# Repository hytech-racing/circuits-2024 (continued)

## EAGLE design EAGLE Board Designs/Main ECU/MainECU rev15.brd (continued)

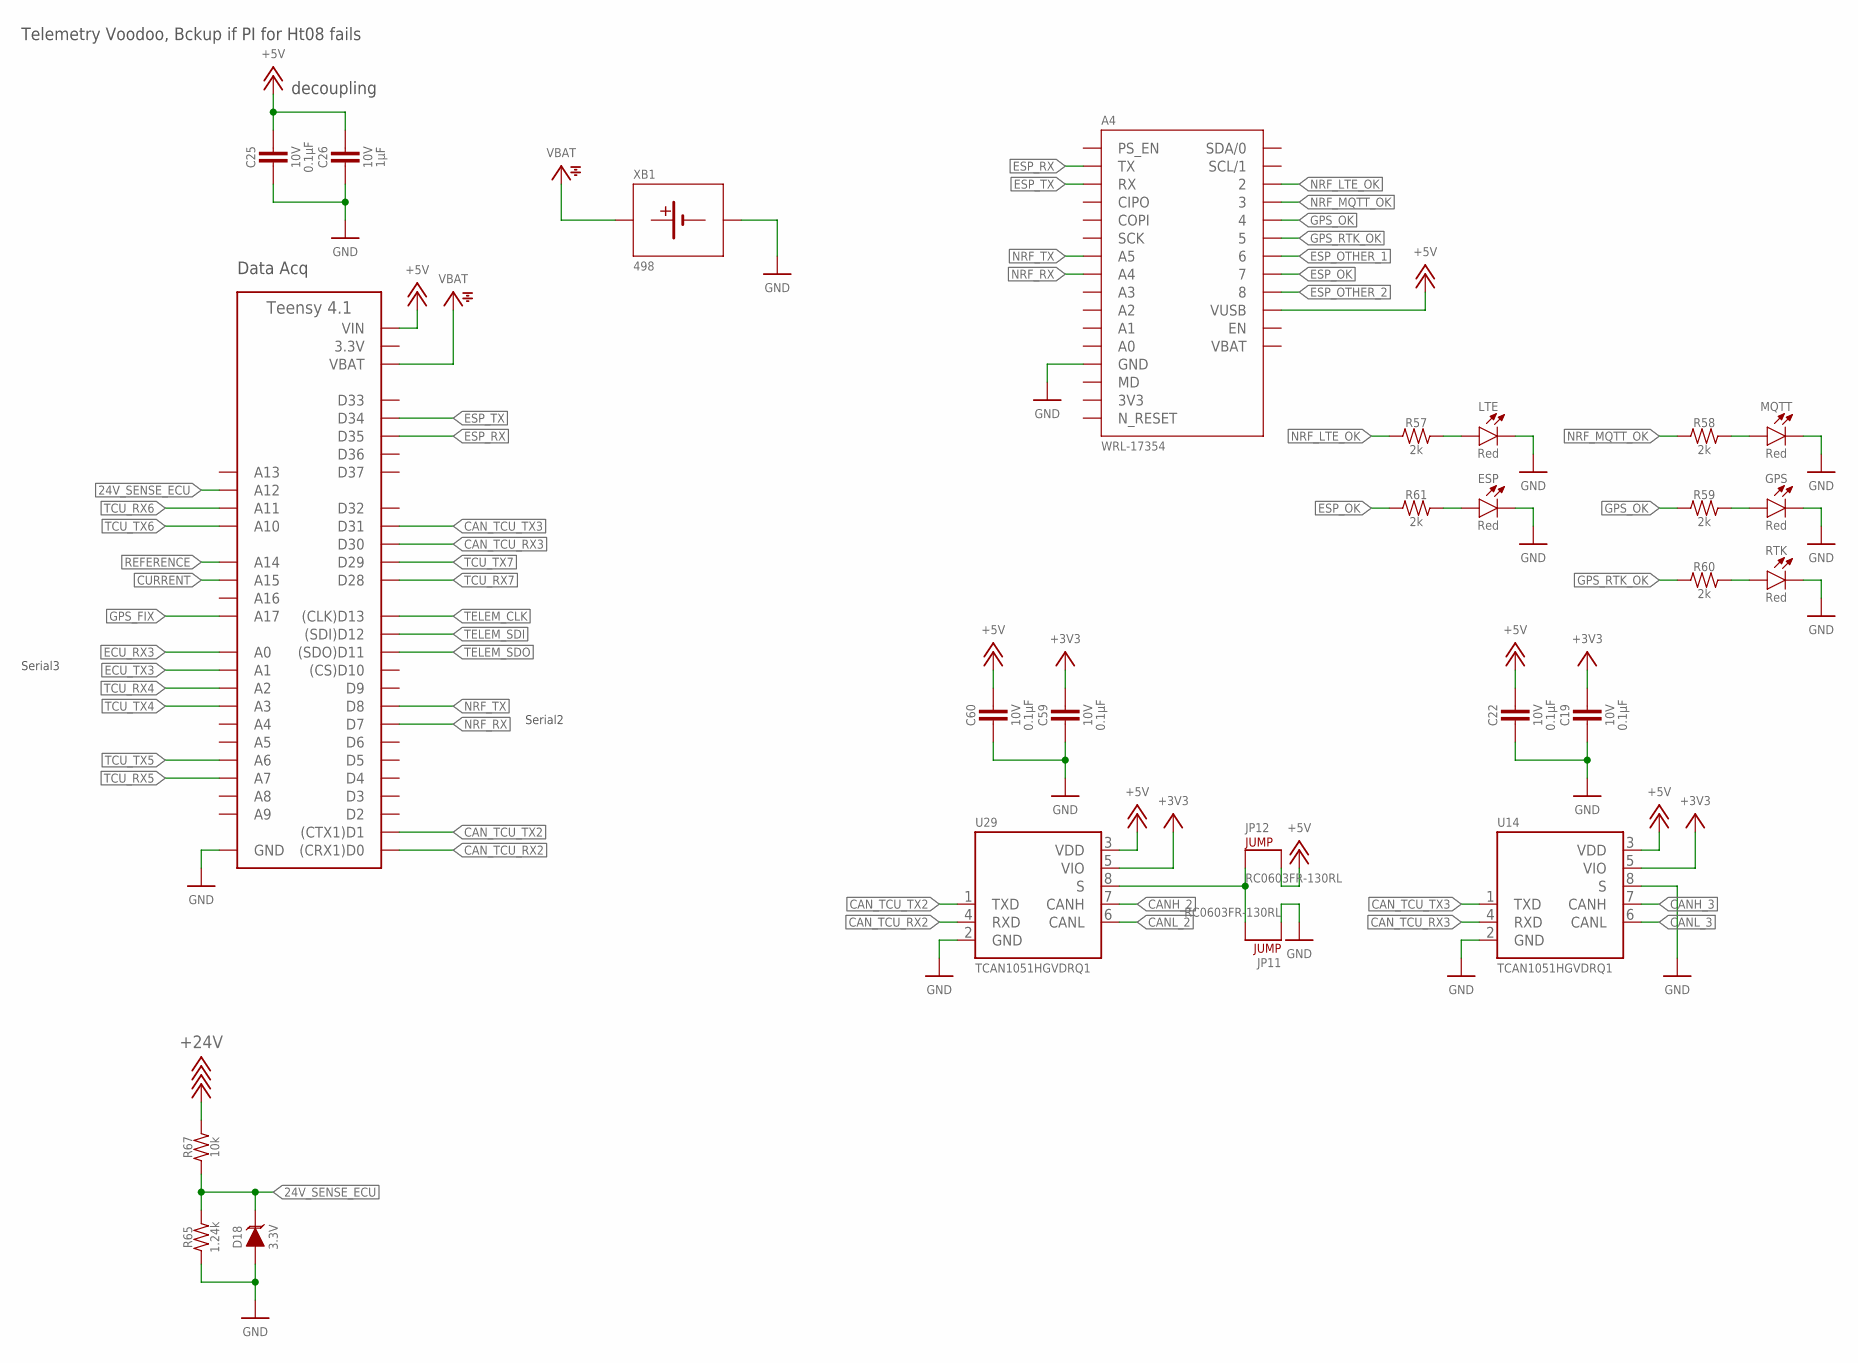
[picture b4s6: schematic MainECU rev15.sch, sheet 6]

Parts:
A3: TEENSY_4.1; TEENSY_LONG_EXT
A4: NRF9160LTE
C19, C22, C25, C59, C60: CAPACITOR_0603_10V_0.1UF; 0603-CAP
C26: CAPACITOR_0603_10V_1UF; 0603-CAP
D18: TVS__5V; SOT-23; VOLTAGE 3.3V; MPN GSOT03-E3-08
ESP: LED_0603_RED; 0603-LED
GPS: LED_0603_RED; 0603-LED
JP11: DNP; 0603-RES
JP12: JUMPER_0603_; 0603-RES
LTE: LED_0603_RED; 0603-LED
MQTT: LED_0603_RED; 0603-LED
R57, R58, R59, R60, R61: RESISTOR_0603_2K; 0603-RES
R65: RESISTOR_0603_1.24K; 0603-RES
R67: RESISTOR_0603_10K; 0603-RES
RTK: LED_0603_RED; 0603-LED
U14, U29: TCAN1051HQV-Q1; SOIC-08(NARROW,0.15")
XB1: BATTERY_HOLDER_KEYSTONE_498; 498

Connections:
3.3V: A3.3V3 (3.3V), A3.3V3@2 (3.3V), A3.3V3@3 (3.3V); also elsewhere on the board
3V3: A4.3V3
24V_SENSE_ECU: A3.D26 (A12), D18.3 (C), R65.2, R67.1; also elsewhere on the board
+3V3: C19.1, C59.1, U14.5 (VIO), U29.5 (VIO); also elsewhere on the board
+5V: A3.VIN, A4.VUSB, C22.1, C25.1, C26.1, C60.1, JP12.2, U14.3 (VDD), U29.3 (VDD); also elsewhere on the board
+24V: R67.2; also elsewhere on the board
CANH_2: U29.7 (CANH); also elsewhere on the board
CANH_3: U14.7 (CANH); also elsewhere on the board
CANL_2: U29.6 (CANL); also elsewhere on the board
CANL_3: U14.6 (CANL); also elsewhere on the board
CAN_TCU_RX2: A3.D0 ((CRX1)D0), U29.4 (RXD)
CAN_TCU_RX3: A3.D30, U14.4 (RXD)
CAN_TCU_TX2: A3.D1 ((CTX1)D1), U29.1 (TXD)
CAN_TCU_TX3: A3.D31, U14.1 (TXD)
CURRENT: A3.D39 (A15); also elsewhere on the board
ECU_RX3: A3.D14 (A0); also elsewhere on the board
ECU_TX3: A3.D15 (A1); also elsewhere on the board
ESP_OK: A4.7, R61.1
ESP_OTHER_1: A4.6
ESP_OTHER_2: A4.8
ESP_RX: A3.D35, A4.TX
ESP_TX: A3.D34, A4.RX
GND: A3.AGND/GND (GND), A3.GND, A3.GND@2 (GND), A4.GND, C19.2, C22.2, C25.2, C26.2, C59.2, C60.2, D18.1 (A), ESP.1 (C), GPS.1 (C), JP11.1, LTE.1 (C), MQTT.1 (C), R65.1, RTK.1 (C), U14.2 (GND), U14.8 (S), U29.2 (GND), XB1.2 (MINUS); also elsewhere on the board
GPS_FIX: A3.D41 (A17)
GPS_OK: A4.4, R59.1
GPS_RTK_OK: A4.5, R60.1
unnamed: ESP.2 (A), R61.2
unnamed: JP11.2, JP12.1, U29.8 (S)
unnamed: LTE.2 (A), R57.2
unnamed: MQTT.2 (A), R58.2
unnamed: GPS.2 (A), R59.2
unnamed: R60.2, RTK.2 (A)
NRF_LTE_OK: A4.2, R57.1
NRF_MQTT_OK: A4.3, R58.1
NRF_RX: A3.D7, A4.A4
NRF_TX: A3.D8, A4.A5
REFERENCE: A3.D38 (A14); also elsewhere on the board
TCU_RX4: A3.D16 (A2)
TCU_RX5: A3.D21 (A7)
TCU_RX6: A3.D25 (A11)
TCU_RX7: A3.D28
TCU_TX4: A3.D17 (A3)
TCU_TX5: A3.D20 (A6)
TCU_TX6: A3.D24 (A10)
TCU_TX7: A3.D29
TELEM_CLK: A3.D13 ((CLK)D13)
TELEM_SDI: A3.D12 ((SDI)D12)
TELEM_SDO: A3.D11 ((SDO)D11)
VBAT: A3.VBAT, A4.VBAT, XB1.1 (PLUS)

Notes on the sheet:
decoupling
Data Acq
Serial2
Serial3
Telemetry Voodoo, Bckup if PI for Ht08 fails

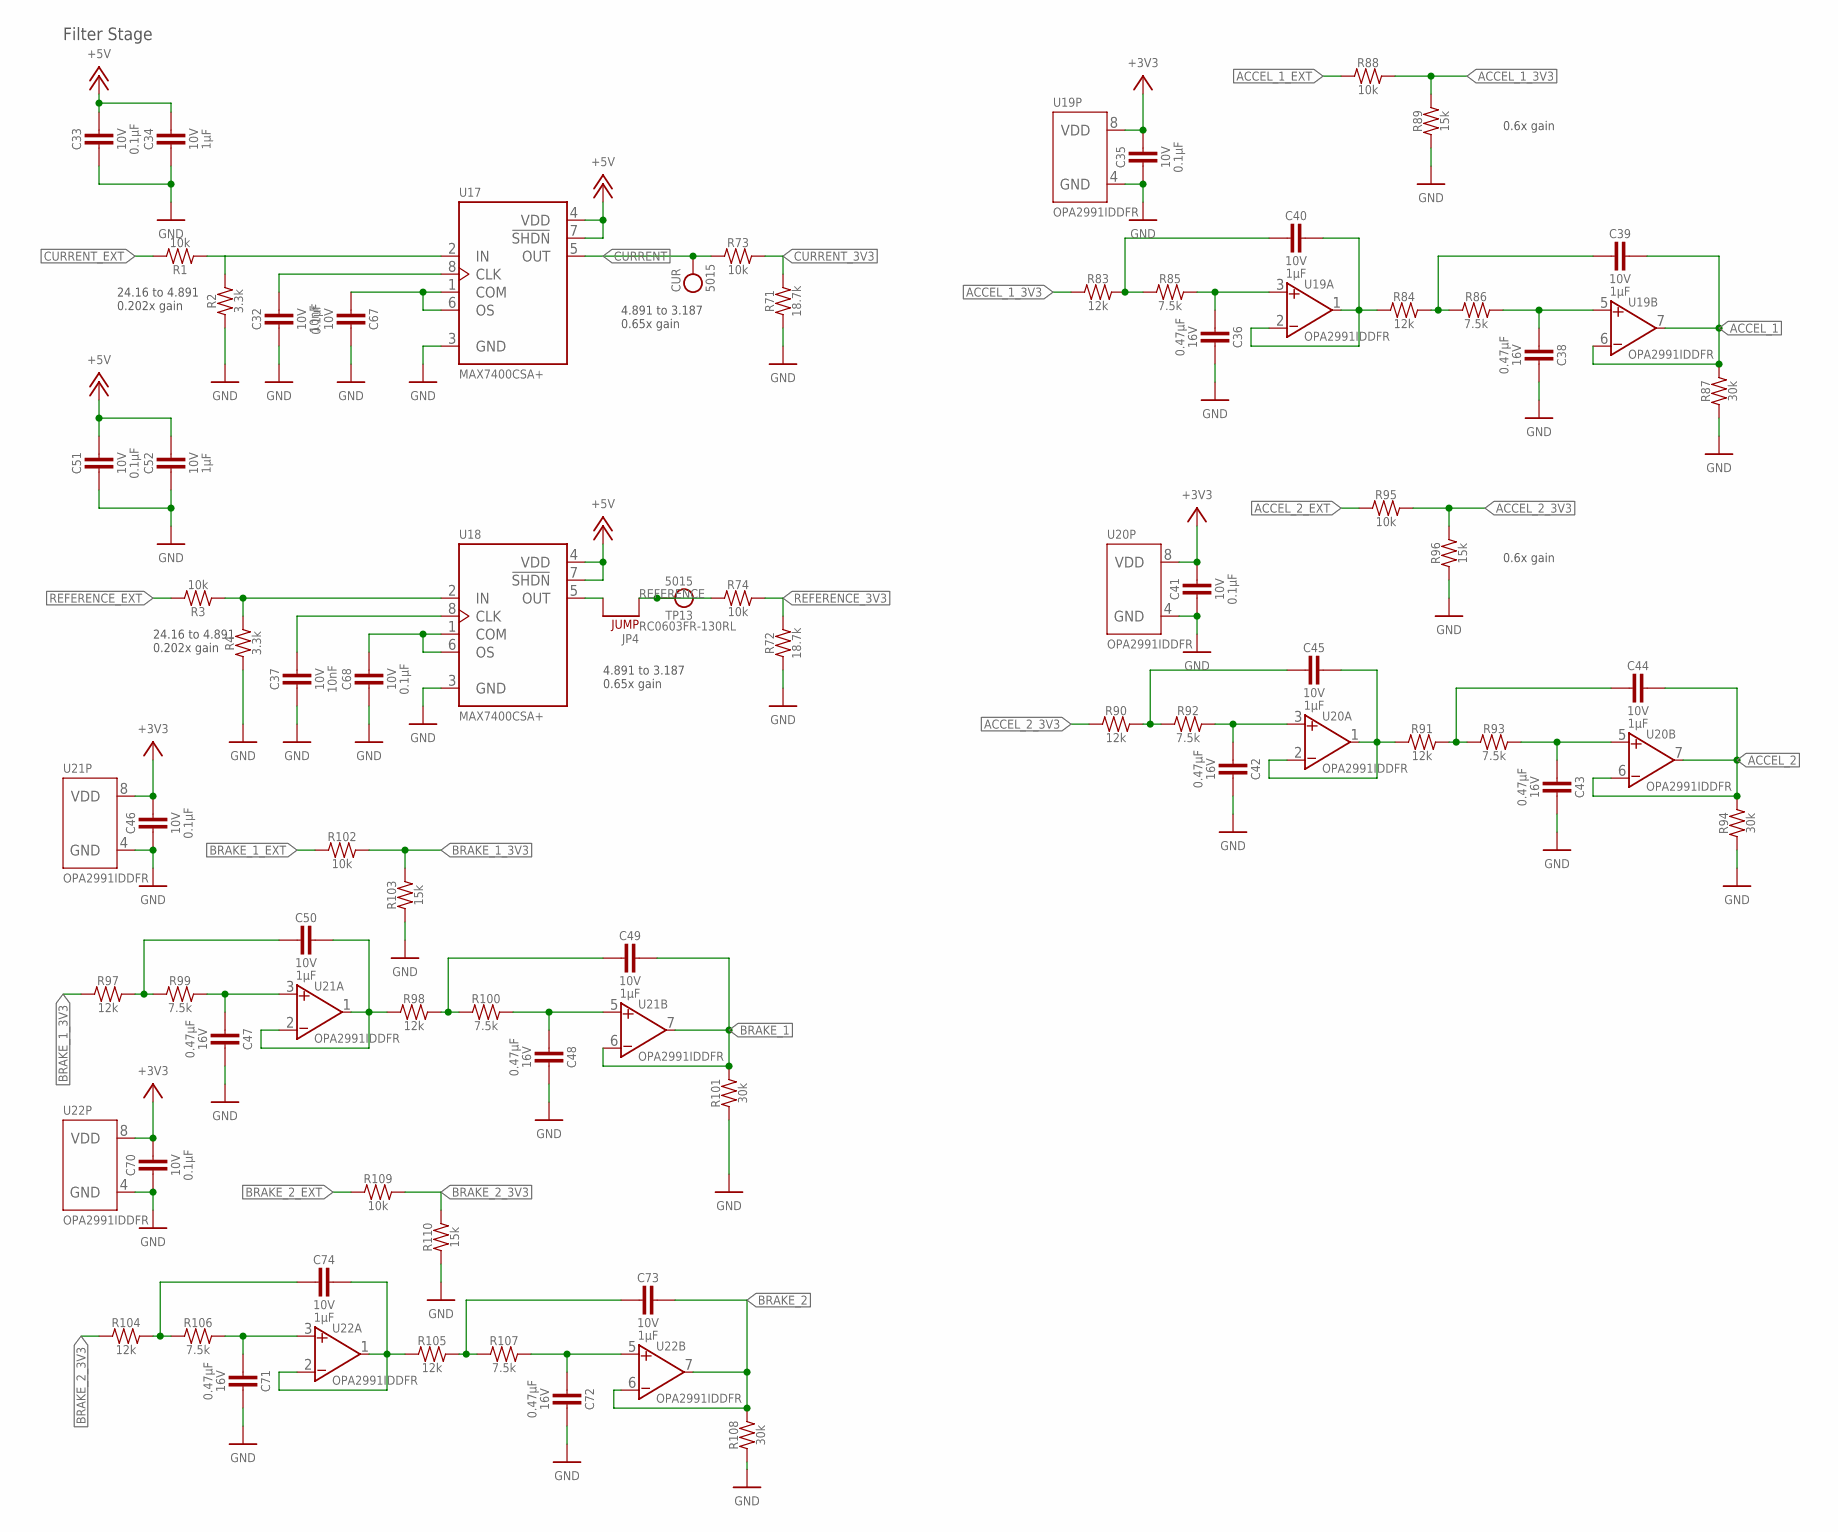
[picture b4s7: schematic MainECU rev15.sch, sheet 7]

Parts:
C32, C37: CAPACITOR_0603_10V_10NF; 0603-CAP
C33, C35, C41, C46, C51, C67, C68, C70: CAPACITOR_0603_10V_0.1UF; 0603-CAP
C34, C39, C40, C44, C45, C49, C50, C52, C73, C74: CAPACITOR_0603_10V_1UF; 0603-CAP
C36, C38, C42, C43, C47, C48, C71, C72: CAPACITOR_0603_16V_0.47UF; 0603-CAP
CUR: TEST_POINT; 5015
JP4: JUMPER_0603_; 0603-RES
R1, R3, R73, R74, R88, R95, R102, R109: RESISTOR_0603_10K; 0603-RES
R2, R4: RESISTOR_0603_3.3K; 0603-RES
R71, R72: RESISTOR_0603_18.7K; 0603-RES
R83, R84, R90, R91, R97, R98, R104, R105: RESISTOR_0603_12K; 0603-RES
R85, R86, R92, R93, R99, R100, R106, R107: RESISTOR_0603_7.5K; 0603-RES
R87, R94, R101, R108: RESISTOR_0603_30K; 0603-RES
R89, R96, R103, R110: RESISTOR_0603_15K; 0603-RES
TP13: TEST_POINT; 5015
U17, U18: MAX7400; SOIC-08(NARROW,0.15")
U19, U20, U21, U22: OPAMP_2_CHANNEL_OPA_2991; SOT-23-8

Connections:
+3V3: C35.1, C41.1, C46.1, C70.1, U19.8 (VDD), U20.8 (VDD), U21.8 (VDD), U22.8 (VDD); also elsewhere on the board
+5V: C33.1, C34.1, C51.1, C52.1, U17.4 (VDD), U17.7 (!SHDN), U18.4 (VDD), U18.7 (!SHDN); also elsewhere on the board
ACCEL_1: C39.1, R87.2, U19.6 (VIN-), U19.7 (VOUT); also elsewhere on the board
ACCEL_1_3V3: R83.1, R88.2, R89.2
ACCEL_1_EXT: R88.1; also elsewhere on the board
ACCEL_2: C44.1, R94.2, U20.6 (VIN-), U20.7 (VOUT); also elsewhere on the board
ACCEL_2_3V3: R90.1, R95.2, R96.2
ACCEL_2_EXT: R95.1; also elsewhere on the board
BRAKE_1: C49.1, R101.2, U21.6 (VIN-), U21.7 (VOUT); also elsewhere on the board
BRAKE_1_3V3: R97.1, R102.2, R103.2
BRAKE_1_EXT: R102.1; also elsewhere on the board
BRAKE_2: C73.1, R108.2, U22.6 (VIN-), U22.7 (VOUT); also elsewhere on the board
BRAKE_2_3V3: R104.1, R109.2, R110.2
BRAKE_2_EXT: R109.1; also elsewhere on the board
CURRENT: CUR.1, R73.1, U17.5 (OUT); also elsewhere on the board
CURRENT_3V3: R71.2, R73.2; also elsewhere on the board
CURRENT_EXT: R1.2; also elsewhere on the board
CURRENT_PRE: R1.1, R2.2, U17.2 (IN)
GND: C32.2, C33.2, C34.2, C35.2, C36.1, C37.2, C38.1, C41.2, C42.1, C43.1, C46.2, C47.1, C48.1, C51.2, C52.2, C67.1, C68.2, C70.2, C71.1, C72.1, R2.1, R4.1, R71.1, R72.1, R87.1, R89.1, R94.1, R96.1, R101.1, R103.1, R108.1, R110.1, U17.3 (GND), U18.3 (GND), U19.4 (GND), U20.4 (GND), U21.4 (GND), U22.4 (GND); also elsewhere on the board
unnamed: C40.2, R83.2, R85.1
unnamed: C36.2, R85.2, U19.3 (VIN+)
unnamed: C39.2, R84.2, R86.1
unnamed: C40.1, R84.1, U19.1 (VOUT), U19.2 (VIN-)
unnamed: C38.2, R86.2, U19.5 (VIN+)
unnamed: C43.2, R93.2, U20.5 (VIN+)
unnamed: JP4.2, U18.5 (OUT)
unnamed: C42.2, R92.2, U20.3 (VIN+)
unnamed: C37.1, U18.8 (CLK)
unnamed: C45.1, R91.1, U20.1 (VOUT), U20.2 (VIN-)
unnamed: C44.2, R91.2, R93.1
unnamed: C45.2, R90.2, R92.1
unnamed: C50.2, R97.2, R99.1
unnamed: C68.1, U18.1 (COM), U18.6 (OS)
unnamed: C32.1, U17.8 (CLK)
unnamed: C47.2, R99.2, U21.3 (VIN+)
unnamed: C67.2, U17.1 (COM), U17.6 (OS)
unnamed: C50.1, R98.1, U21.1 (VOUT), U21.2 (VIN-)
unnamed: C49.2, R98.2, R100.1
unnamed: C48.2, R100.2, U21.5 (VIN+)
unnamed: C74.2, R104.2, R106.1
unnamed: C71.2, R106.2, U22.3 (VIN+)
unnamed: C74.1, R105.1, U22.1 (VOUT), U22.2 (VIN-)
unnamed: C73.2, R105.2, R107.1
unnamed: C72.2, R107.2, U22.5 (VIN+)
REFERENCE: JP4.1, R74.1, TP13.1; also elsewhere on the board
REFERENCE_3V3: R72.2, R74.2; also elsewhere on the board
REFERENCE_EXT: R3.2; also elsewhere on the board
REFERNECE_PRE: R3.1, R4.2, U18.2 (IN)

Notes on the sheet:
24.16 to 4.891 0.202x gain
Filter Stage
4.891 to 3.187 0.65x gain
0.6x gain

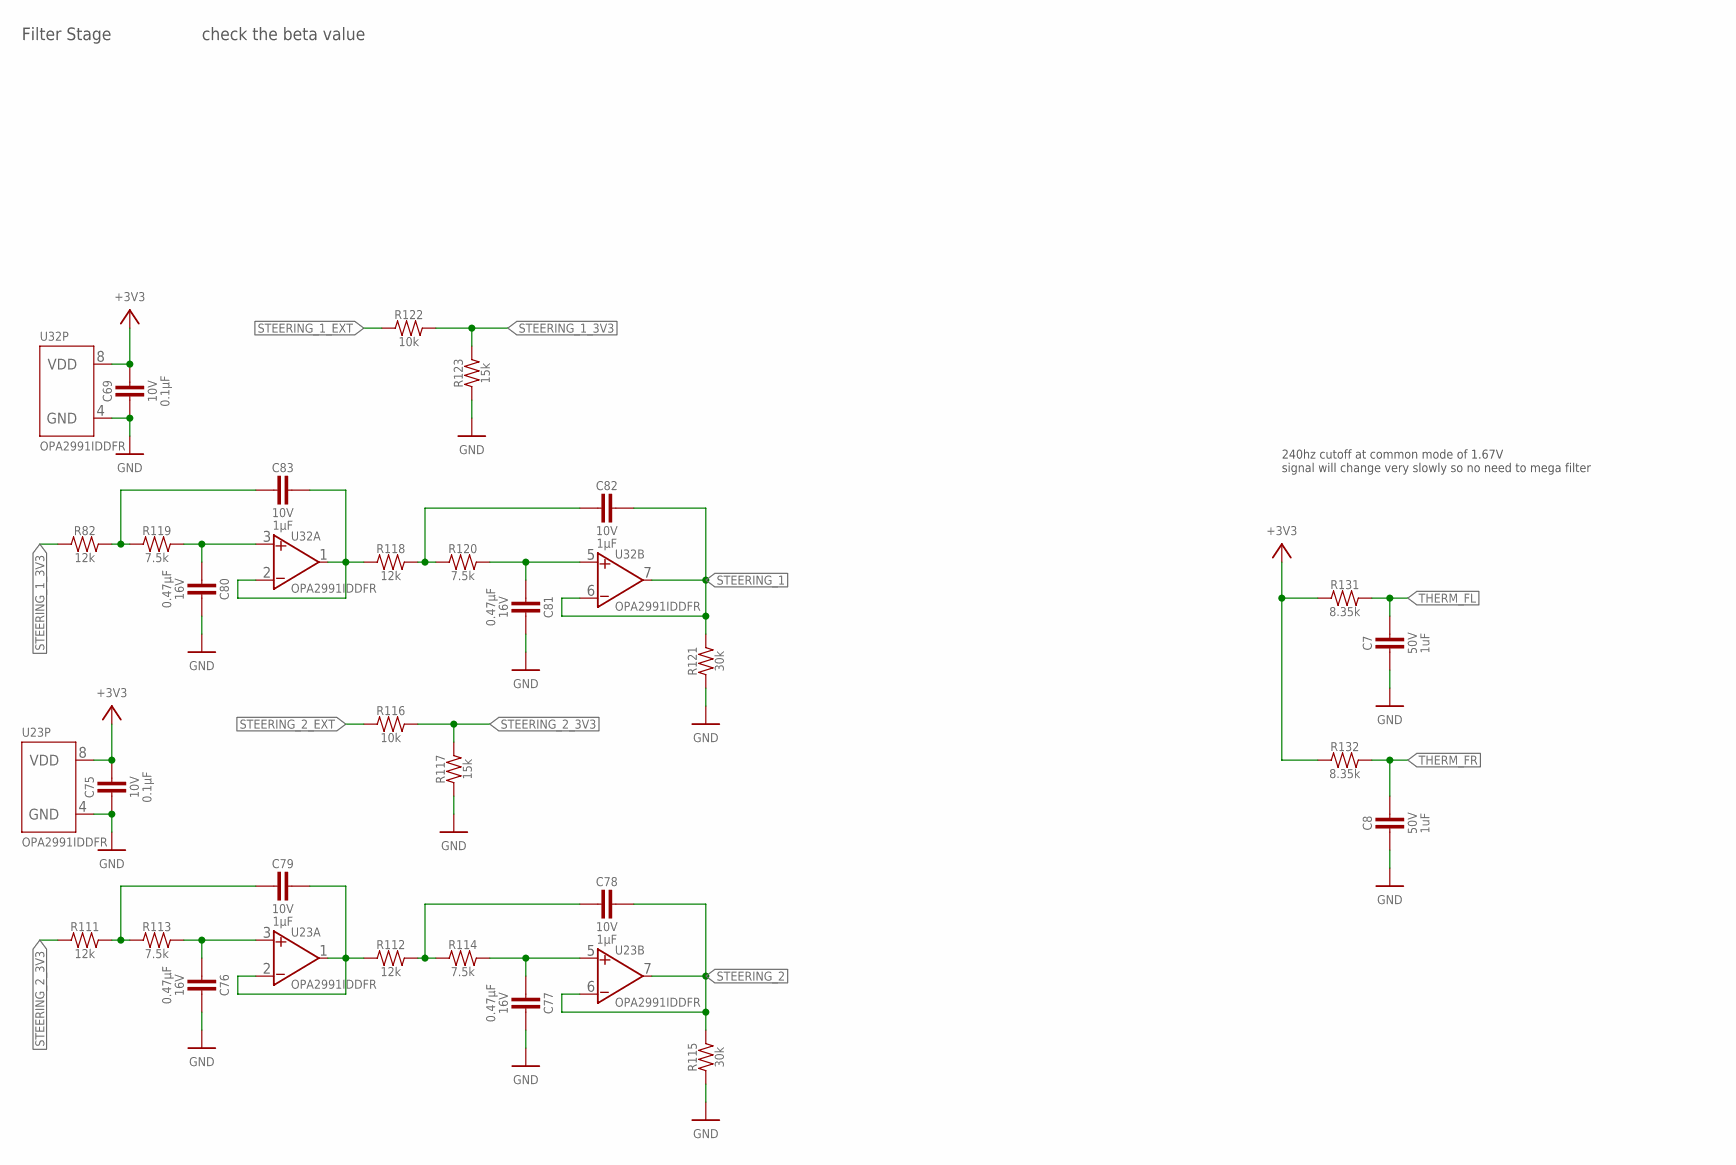
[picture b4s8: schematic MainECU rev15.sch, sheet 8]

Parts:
C7, C8: CAPACITOR_0603_50V_1UF; 0603-CAP
C69, C75: CAPACITOR_0603_10V_0.1UF; 0603-CAP
C76, C77, C80, C81: CAPACITOR_0603_16V_0.47UF; 0603-CAP
C78, C79, C82, C83: CAPACITOR_0603_10V_1UF; 0603-CAP
R82, R111, R112, R118: RESISTOR_0603_12K; 0603-RES
R113, R114, R119, R120: RESISTOR_0603_7.5K; 0603-RES
R115, R121: RESISTOR_0603_30K; 0603-RES
R116, R122: RESISTOR_0603_10K; 0603-RES
R117, R123: RESISTOR_0603_15K; 0603-RES
R131, R132: RESISTOR_0603_8.35K; 0603-RES
U23, U32: OPAMP_2_CHANNEL_OPA_2991; SOT-23-8

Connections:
+3V3: C69.1, C75.1, R131.1, R132.1, U23.8 (VDD), U32.8 (VDD); also elsewhere on the board
GND: C7.2, C8.2, C69.2, C75.2, C76.1, C77.1, C80.1, C81.1, R115.1, R117.1, R121.1, R123.1, U23.4 (GND), U32.4 (GND); also elsewhere on the board
unnamed: C83.2, R82.2, R119.1
unnamed: C80.2, R119.2, U32.3 (VIN+)
unnamed: C83.1, R118.1, U32.1 (VOUT), U32.2 (VIN-)
unnamed: C82.2, R118.2, R120.1
unnamed: C81.2, R120.2, U32.5 (VIN+)
unnamed: C79.2, R111.2, R113.1
unnamed: C76.2, R113.2, U23.3 (VIN+)
unnamed: C79.1, R112.1, U23.1 (VOUT), U23.2 (VIN-)
unnamed: C78.2, R112.2, R114.1
unnamed: C77.2, R114.2, U23.5 (VIN+)
STEERING_1: C82.1, R121.2, U32.6 (VIN-), U32.7 (VOUT); also elsewhere on the board
STEERING_1_3V3: R82.1, R122.2, R123.2
STEERING_1_EXT: R122.1; also elsewhere on the board
STEERING_2: C78.1, R115.2, U23.6 (VIN-), U23.7 (VOUT); also elsewhere on the board
STEERING_2_3V3: R111.1, R116.2, R117.2
STEERING_2_EXT: R116.1; also elsewhere on the board
THERM_FL: C7.1, R131.2; also elsewhere on the board
THERM_FR: C8.1, R132.2; also elsewhere on the board

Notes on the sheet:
Filter Stage
check the beta value
240hz cutoff at common mode of 1.67V signal will change very slowly so no need to mega filter

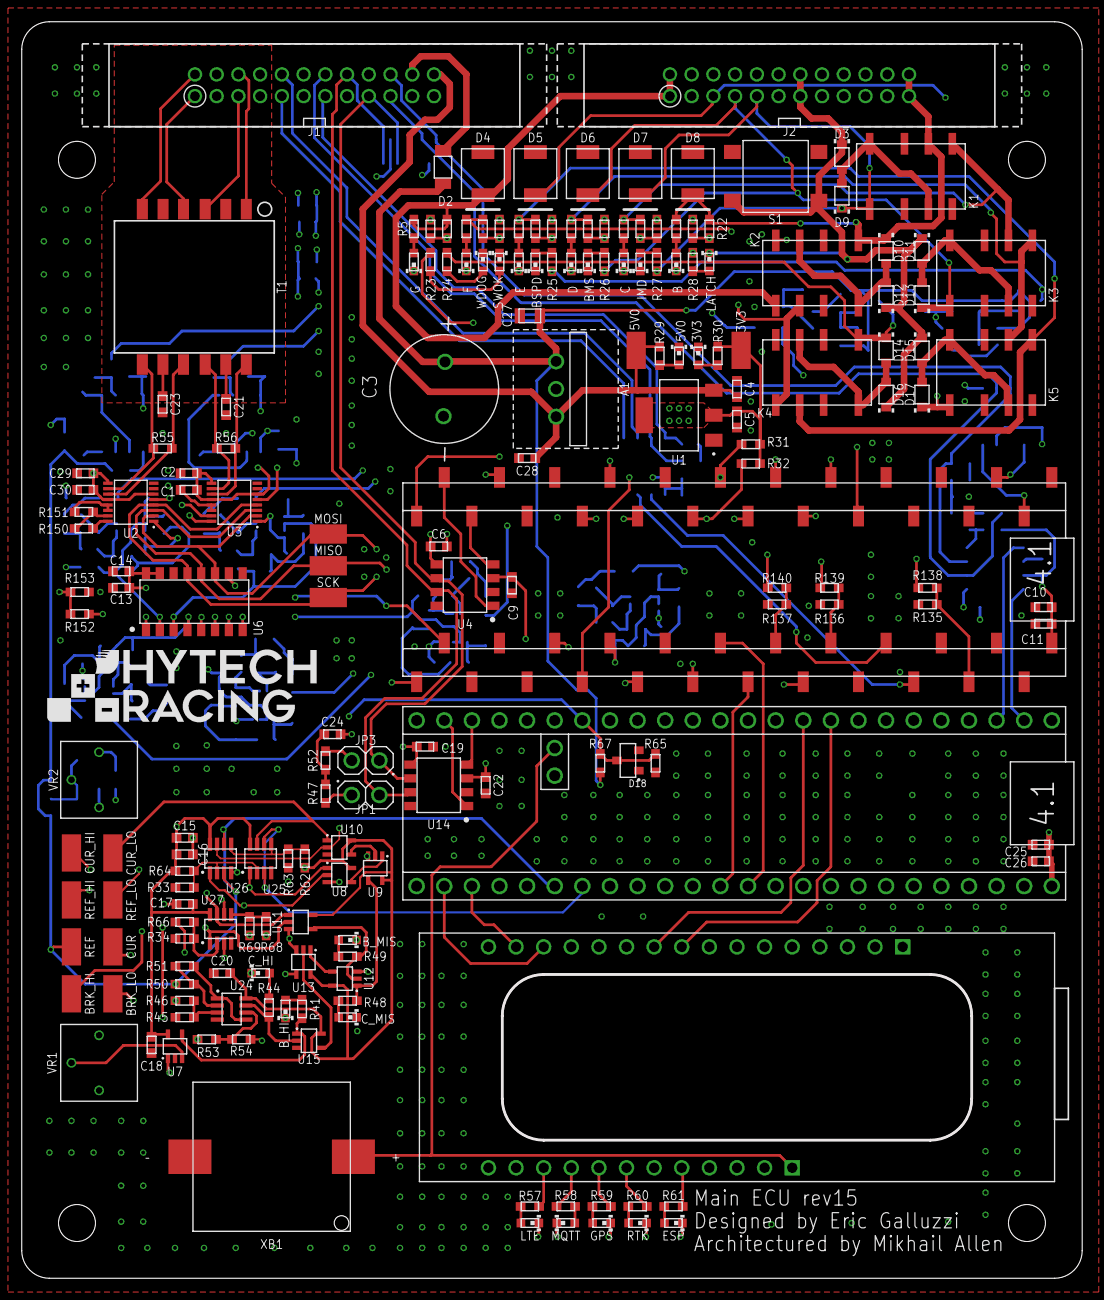
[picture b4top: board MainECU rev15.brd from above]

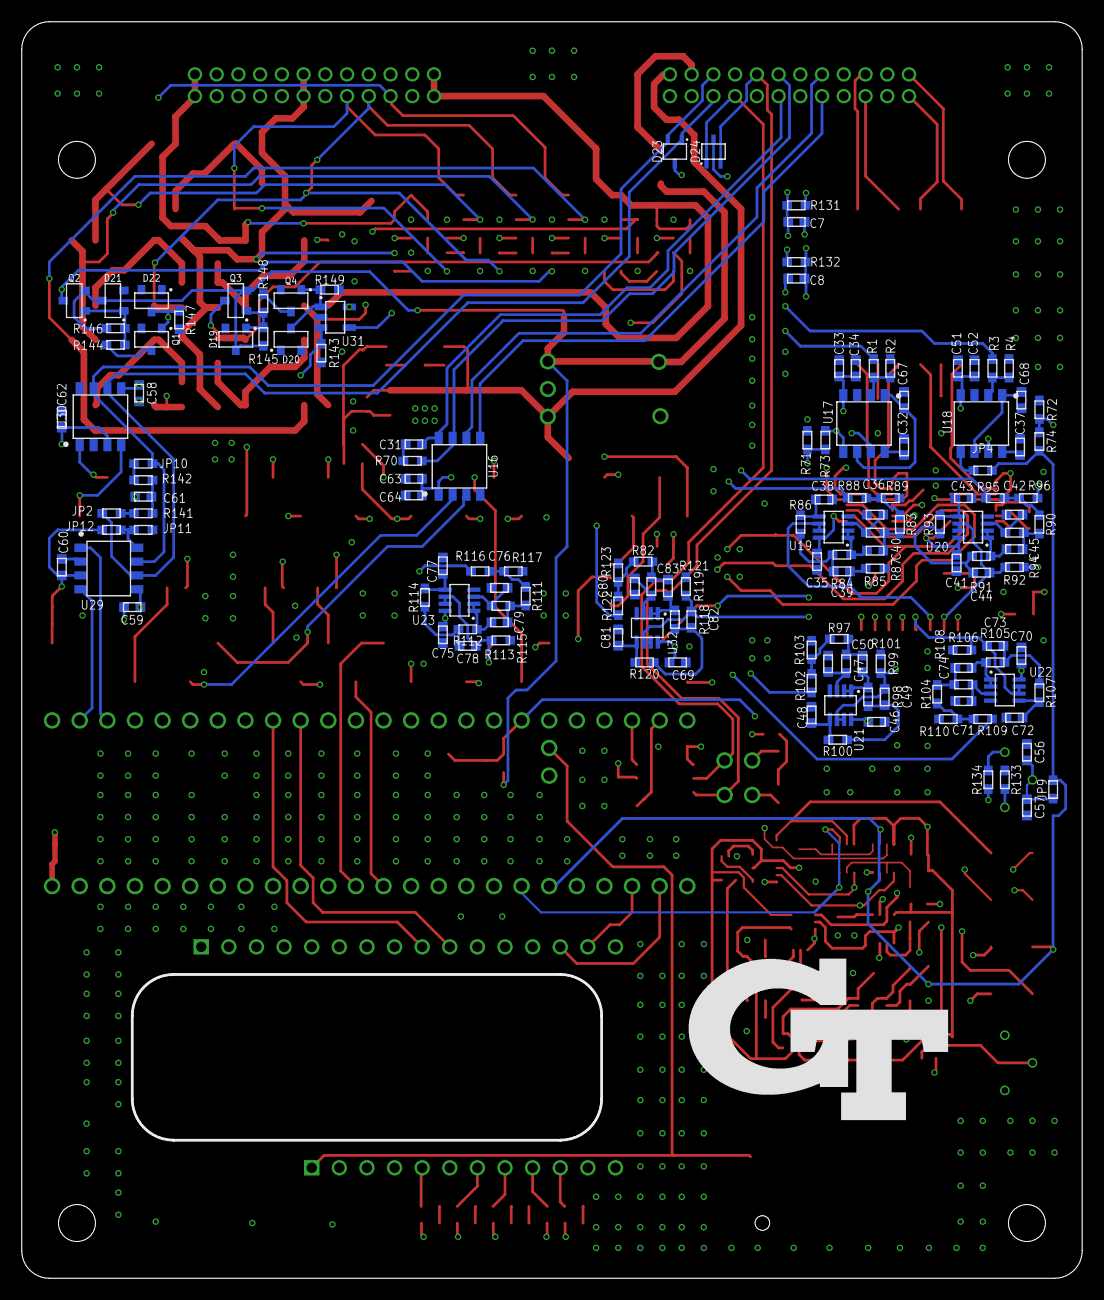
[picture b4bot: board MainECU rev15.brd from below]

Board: 6 copper layers, 97.5 x 115.6 mm, 331 parts (143 on the bottom side), 214 nets.

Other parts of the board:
$$$$U$1, $$$$U$2: MOUNTING_M3
$$U$2: MOUNTING_M3
U$1: MOUNTING_M3
U$3: LOGO_HYTECH_MEDIUM
U$5: LOGO_GT_LARGE

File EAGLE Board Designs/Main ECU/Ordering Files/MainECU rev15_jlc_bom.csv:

Comment,Designator,Footprint,LCSC Part #
BATTERY_HOLDER_KEYSTONE_498,XB1,498,
BUTTON,S1,B3S-100X,
CAPACITOR_0603_10V_0.1UF,C1 C6 C9 C10 C14 C15 C16 C17 C18 C19 C20 C22 C25 C29,0603-CAP,
CAPACITOR_0603_10V_1UF,C2 C11 C13 C26 C30,0603-CAP,
CAPACITOR_0603_10V_4.7NF,C24,0603-CAP,
CAPACITOR_0603_10V_15PF,C21 C23,0603-CAP,
CAPACITOR_0603_25V_10UF,C4 C5 C28,0603-CAP,
CAPACITOR_0805_50V_10UF,C27,0805-CAP,
LED_0603_GREEN,B BSPD C D E F G,0603-LED,
LED_0603_ORANGE,BMS IMD SWOK WDOG,0603-LED,
LED_0603_RED,B_HI B_MIS C_HI C_MIS ESP GPS LTE MQTT RTK,0603-LED,
LED_0603_WHITE,LATCH,0603-LED,
LED_0603_YELLOW,3V3 5V0,0603-LED,
LOGICGATE_AND_DCK3,U15,SC-70-5,
LOGICGATE_NOR,U13,SC-70-5,
LOGICGATE_OR,U8 U9 U10 U11 U12,SC-70-5,
LTC6820,U2 U3,MSOP-16,
MCP3208,U6,SOIC-16,
OPAMP_1_CHANNEL_OPA991,U7,SC-70-5,
OPAMP_2_CHANNEL_OPA_2991,U24 U25 U26 U27,SOT-23-8,
RELAY_DPDT_07DSMT,K1 K2 K3 K4 K5,IM*G,
RESISTOR_0603_1.13K,R63 R64 R151 R153,0603-RES,
RESISTOR_0603_1.24K,R65,0603-RES,
RESISTOR_0603_1.33K,R150 R152,0603-RES,
RESISTOR_0603_1K,R46 R50,0603-RES,
RESISTOR_0603_2.18K,R68,0603-RES,
RESISTOR_0603_2.55K,R66,0603-RES,
RESISTOR_0603_2K,R5 R8 R11 R14 R17 R20 R24 R25 R26 R27 R31 R32 R57 R58 R59 R60 R61,0603-RES,
RESISTOR_0603_4.64K,R6 R9 R12 R15 R18 R21 R135 R136 R137,0603-RES,
RESISTOR_0603_10.2K,R33 R34 R62,0603-RES,
RESISTOR_0603_10K,R54 R67 R69,0603-RES,
RESISTOR_0603_14K,R53,0603-RES,
RESISTOR_0603_36.5K,R7 R10 R13 R16 R19 R22 R138 R139 R140,0603-RES,
RESISTOR_0603_43K,R45 R51,0603-RES,
RESISTOR_0603_60.4,R47 R52,0603-RES,
RESISTOR_0603_120,R23 R30 R55 R56,0603-RES,
RESISTOR_0603_180,R28,0603-RES,
RESISTOR_0603_240,R29 R41 R44 R48 R49,0603-RES,
SCHOTTKY_1206_40V,D2,1206-DIODE,
SCHOTTKY_SOD323_30V,D3 D9 D10 D11 D12 D13 D14 D15 D16 D17,SOD-323,
TCAN1051HQV-Q1,U4,"SOIC-08(NARROW 0.15"")",
TCAN1051HQV-Q1,U14,"SOIC-08(NARROW 0.15"")",
TEENSY_4.1_SMT,A2,TEENSY_LONG_SSM,
TEST_POINT,CUR TP1 TP2 TP3 TP4 TP6 TP7 TP8 TP9 TP10 TP11 TP12 TP13,5015,
TRANSFORMER_HM2112ZNLT,T1,HM2112ZNLT,
TVS_DO-214AA_30V,D4 D5 D6 D7 D8,1.5SMBJ,
TVS__5V,D18,SOT-23,
VOLTAGE_REGULATOR_SOT-223_3.3V,U1,SOT-223,
ADM8316WBX30,U31,SOT-23-5,
CAPACITOR_0603_10V_0.1UF,C33 C35 C41 C46 C51 C57 C58 C59 C60 C62 C63 C67 C68 C69 C70 C75,0603-CAP,
CAPACITOR_0603_10V_1UF,C34 C39 C40 C44 C45 C49 C50 C52 C56 C64 C73 C74 C78 C79 C82 C83,0603-CAP,
CAPACITOR_0603_10V_4.7NF,C61,0603-CAP,
CAPACITOR_0603_10V_10NF,C32 C37,0603-CAP,
CAPACITOR_0603_16V_0.47UF,C36 C38 C42 C43 C47 C48 C71 C72 C76 C77 C80 C81,0603-CAP,
CAPACITOR_0603_25V_1.2NF,C31,0603-CAP,
CAPACITOR_0603_50V_1UF,C7 C8,0603-CAP,
DNP,JP9 JP11,0603-RES,
JUMPER_0603_,JP2 JP4 JP10 JP12,0603-RES,
MAX3074EESA+,U16,"SOIC-08(NARROW 0.15"")",
MAX7400,U17,"SOIC-08(NARROW 0.15"")",
MAX7400,U18,"SOIC-08(NARROW 0.15"")",
OPAMP_2_CHANNEL_OPA_2991,U19 U20 U21 U22 U23 U32,SOT-23-8,
RESISTOR_0603_3.3K,R2 R4,0603-RES,
RESISTOR_0603_5.1K,R144 R145 R146 R148,0603-RES,
RESISTOR_0603_7.5K,R85 R86 R92 R93 R99 R100 R106 R107 R113 R114 R119 R120,0603-RES,
RESISTOR_0603_8.35K,R131 R132,0603-RES,
RESISTOR_0603_10K,R1 R3 R73 R74 R88 R95 R102 R109 R116 R122 R133 R134 R143 R147 R149,0603-RES,
RESISTOR_0603_12K,R82 R83 R84 R90 R91 R97 R98 R104 R105 R111 R112 R118,0603-RES,
RESISTOR_0603_15K,R89 R96 R103 R110 R117 R123,0603-RES,
RESISTOR_0603_18.7K,R71 R72,0603-RES,
RESISTOR_0603_30K,R87 R94 R101 R108 R115 R121,0603-RES,
RESISTOR_0603_60.4,R141 R142,0603-RES,
RESISTOR_0603_DNP,R70,0603-RES,
TCAN1051HQV-Q1,U29,"SOIC-08(NARROW 0.15"")",
TCAN1051HQV-Q1,U30,"SOIC-08(NARROW 0.15"")",
TRANSISTOR_N_MOS__DMG3406L-7,Q1 Q4,SOT-23,
TRANSISTOR_P_MOS_SOT-23_DMP3056L-7,Q2 Q3,SOT-23,
TVS_BIDIRECTIONAL_DUAL,D23 D24,SC-70-3,
TVS__15V,D19 D20 D21 D22,SOT-23,

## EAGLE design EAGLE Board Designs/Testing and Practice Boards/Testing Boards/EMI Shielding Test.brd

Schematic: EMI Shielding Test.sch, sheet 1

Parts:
C1: CAPACITOR_0603_25V_0.22UF; 0603-CAP
C2, C3, C10, C11: CAPACITOR_0603_25V_0.1UF; 0603-CAP
C4, C5: CAPACITOR_0603_25V_1UF; 0603-CAP
C6: CAPACITOR_0603_10V_4.7UF; 0603-CAP
C7: CAPACITOR_0603_10V_0.1UF; 0603-CAP
C8: CAPACITOR_0603_50V_1UF; 0603-CAP
C9: CAPACITOR_0603_50V_10NF; 0603-CAP
C12, C13, C14: CAPACITOR_1206_35V_22UF; 1206-CAP
J1: CONNECTOR-2_MICROFIT_SMD_RIGHTANGLE_02_SINGLE_BLA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; MOLEX_MICROFIT_SMD_RIGHTANGLE_02_SINGLE
J2: CONNECTOR-4_μF_S_RA_; MOLEX_MICROFIT_SMD_RIGHTANGLE_04_DUAL
R1: RESISTOR_0805_1M; 0805-RES
R2, R3: RESISTOR_0805_365K; 0805-RES
R4, R5: RESISTOR_0805_HV75K; 0805-RES
R6, R7: RESISTOR_0603_13K; 0603-RES
R8: RESISTOR_0603_33.2K; 0603-RES
R9, R10: RESISTOR_0603_10.5K; 0603-RES
R11, R12: RESISTOR_0603_10K; 0603-RES
R13: RESISTOR_0603_73.2K; 0603-RES
R14: RESISTOR_0603_8.66K; 0603-RES
R15: RESISTOR_0603_1M; 0603-RES
U1: VOLTAGE_REGULATOR_ISO_PQP1-D_; PQP1-D
U2: ISO224A_AIRGAP; SOIC-08(WIDE,0.295")-AIRGAP
U3: VOLTAGE_REGULATOR_SOT-23-5_5V; SOT-23-5
U4, U5: OPAMP_1_CHANNEL_OPA991; SC-70-5

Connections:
0.525V_DIV: R13.1, R14.2, R15.2, U5.3 (VIN-)
+5V: C3.1, C5.1, C6.1, C7.1, C10.1, C11.1, R13.2, U2.8 (VDD2), U3.3 (OUT), U4.5 (VDD), U5.5 (VDD)
+24V: C8.1, C12.1, C13.1, J2.1, U1.4 (IN+), U3.2 (IN)
GND: C3.2, C5.2, C6.2, C7.2, C8.2, C10.2, C11.2, C12.2, C13.2, J2.3, R7.2, R11.1, R12.1, R14.1, R15.1, U1.1 (IN-), U2.5 (GND2), U3.1 (GND), U4.2 (GND), U5.2 (GND)
unnamed: C1.1, U2.1 (VCAP)
unnamed: R7.1, R9.2, U4.1 (VIN+)
unnamed: R6.1, R10.2, U4.3 (VIN-)
unnamed: R2.1, R3.2
unnamed: R1.1, R2.2
unnamed: R10.1, R11.2, U2.6 (OUTN)
unnamed: R9.1, U2.7 (OUTP)
TS+12V: C2.1, C4.1, C14.1, U1.5 (OUT+), U2.3 (VDD1)
TS+UNFUSED: J1.1, R1.2
TS-UNFUSED: C1.2, C2.2, C4.2, C9.2, C14.2, J1.2, R4.1, R5.1, U1.7 (OUT-), U2.4 (GND1)
TS_ACTIVE_GLV: J2.2, U5.4 (VOUT)
TS_DIVIDED: R3.1, R4.2, R5.2, R8.1
TS_FILTERED: C9.1, R8.2, U2.2 (IN)
TS_ISO: R6.2, R12.2, U4.4 (VOUT), U5.1 (VIN+)

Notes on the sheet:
530V->11.1V divider 0.02097 factor
550V corresponds to 4.816V out of difference op amp
Trips at 59.95V

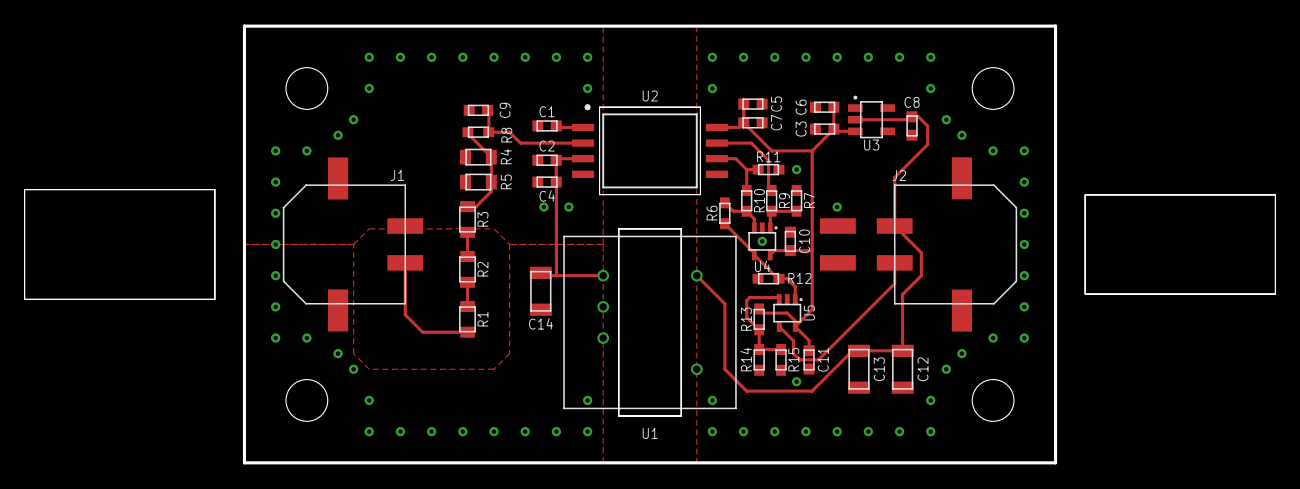
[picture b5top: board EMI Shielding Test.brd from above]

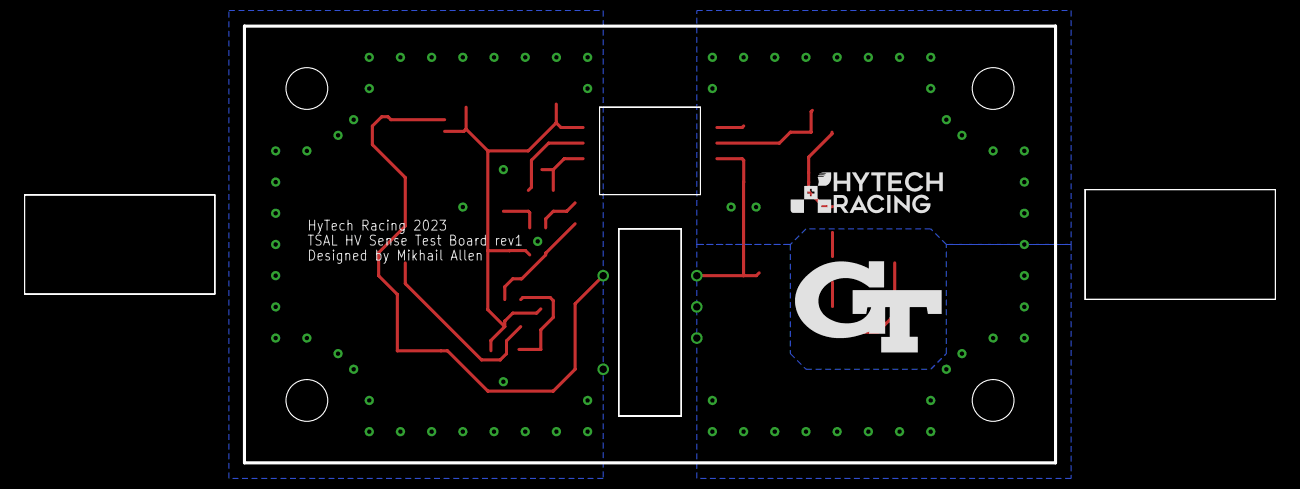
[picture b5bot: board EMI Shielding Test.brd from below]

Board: 2 copper layers, 66.0 x 35.6 mm, 42 parts (2 on the bottom side), 18 nets.

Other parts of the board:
U$5, U$6, U$7, U$8: MOUNTING_M3
U$10: LOGO_GT_MEDIUM
U$11: LOGO_HYTECH_SMALL

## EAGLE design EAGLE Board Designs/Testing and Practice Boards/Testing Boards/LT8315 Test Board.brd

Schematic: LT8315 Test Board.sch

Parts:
C1: CAPACITOR_0603_10V_82PF; 0603-CAP
C2, C5: CAPACITOR_0603_25V_10UF; 0603-CAP
C3: CAPACITOR_0603_50V_10NF; 0603-CAP
C4: CAPACITOR_0603_50V_470PF; 0603-CAP
C6: CAPACITOR_0805_50V_10UF; 0805-CAP
C7: CAPACITOR_0603_100V_0.1UF; 0603-CAP
C8: CAPACITOR__0.1UF; 1812-CAP
C9, C10: CAPACITOR_1206_25V_33UF; 1206-CAP
D1: TVS_SOD323F; SOD323F
D2: RECTIFIER__SMA; SMA
D3, D4: RECTIFIER_400V_SOD123; SOD123F
D5: LED_0603_GREEN; 0603-LED
J1, J2: CONNECTOR-2_μF_T_V_BLACK; MOLEX_MICROFIT_PTH_VERTICAL_02_DUAL
R1: RESISTOR_0603_10K; 0603-RES
R2: RESISTOR_0603_75K; 0603-RES
R3: RESISTOR_0603_20K; 0603-RES
R4: RESISTOR_0603_620; 0603-RES
R5: RESISTOR_0603_100K; 0603-RES
R6: RESISTOR_0603_43K; 0603-RES
R7: RESISTOR_0603_0.5; 0603-RES
R8: RESISTOR_0603_1K; 0603-RES
T1: TRANSFORMER(3W); PQ2620
TP1, TP2, TP3, TP4, TP5: TEST_POINT; 5015
U1: LT8315; TSSP-20(16)

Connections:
+12V: C6.1, C7.1, C9.1, C10.1, D4.C, J2.1, R8.2, TP4.1
AUX: C2.1, R4.1, TP1.1, U1.9 (BIAS), U1.17 (EN/UVLO)
GND: C6.2, C7.2, C9.2, C10.2, D5.1 (C), J2.2, T1.10 (10,11), T1.11 (10,11), TP5.1
unnamed: D1.C, D2.C
unnamed: D2.A, T1.1, U1.1 (DRAIN), U1.2 (DRAIN), U1.3 (DRAIN)
unnamed: D3.C, R4.2
unnamed: R1.2, R2.1, U1.12 (FB)
unnamed: C1.1, D3.A, R2.2, T1.5
unnamed: C1.2, R3.2
unnamed: R3.1, U1.10 (DCM)
unnamed: R7.2, U1.18 (SOURCE)
unnamed: C3.1, R5.2, U1.13 (VC)
unnamed: R6.2, U1.14 (IREG)
unnamed: C5.1, U1.8 (INTVCC)
unnamed: D4.A, T1.8 (8,9), T1.9 (8,9)
unnamed: C4.1, R5.1
unnamed: D5.2 (A), R8.1
TS+UNFUSED: C8.1, D1.A, J1.1, T1.3, TP2.1
TS-UNFUSED: C2.2, C3.2, C4.2, C5.2, C8.2, J1.2, R1.1, R6.1, R7.1, T1.6, TP3.1, U1.15 (GND), U1.16 (SMODE), U1.19 (GND), U1.20 (GND), U1.P$1 (GND)

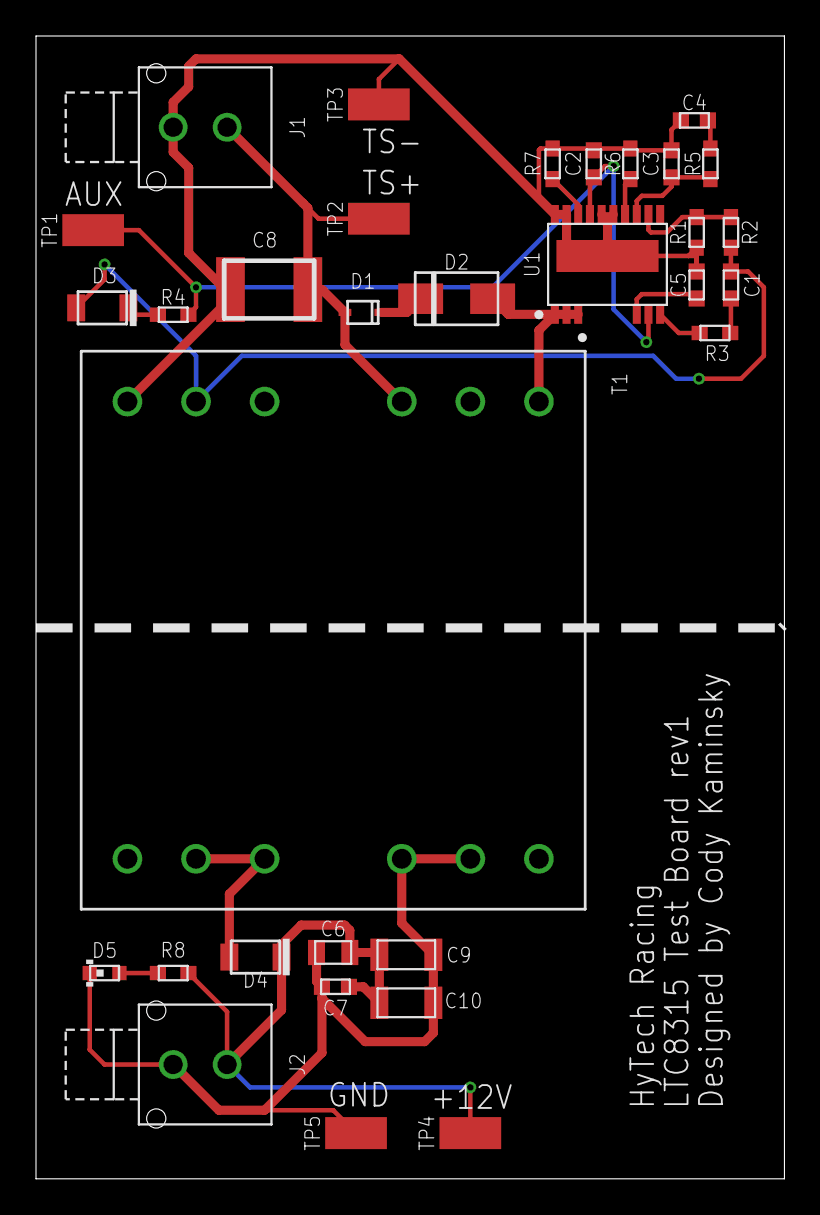
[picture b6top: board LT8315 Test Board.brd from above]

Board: 2 copper layers, 41.6 x 63.5 mm, 32 parts (0 on the bottom side), 19 nets.

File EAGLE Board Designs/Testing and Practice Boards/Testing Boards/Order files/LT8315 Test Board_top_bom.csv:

Comment,Designator,Footprint,LCSC Part #
CAPACITOR_0603_10V_82PF,C1,0603-CAP,
CAPACITOR_0603_25V_10UF,C2 C5,0603-CAP,
CAPACITOR_0603_50V_10NF,C3,0603-CAP,
CAPACITOR_0603_50V_470PF,C4,0603-CAP,
CAPACITOR_0603_100V_0.1UF,C7,0603-CAP,
CAPACITOR_0805_50V_10UF,C6,0805-CAP,
CAPACITOR_1206_25V_33UF,C9 C10,1206-CAP,
CAPACITOR__0.1UF,C8,1812-CAP,
LED_0603_GREEN,D5,0603-LED,
LT8315,U1,TSSP-20(16),
RECTIFIER_400V_SOD123,D3,SOD123F,
RECTIFIER__SMA,D2,SMA,
RESISTOR_0603_0.5,R7,0603-RES,
RESISTOR_0603_1K,R8,0603-RES,
RESISTOR_0603_10K,R1,0603-RES,
RESISTOR_0603_20K,R3,0603-RES,
RESISTOR_0603_43K,R6,0603-RES,
RESISTOR_0603_75K,R2,0603-RES,
RESISTOR_0603_100K,R5,0603-RES,
RESISTOR_0603_620,R4,0603-RES,
SCHOTTKY_SOD323_60V,D4,SOD-323,
TEST_POINT,TP1 TP2 TP3 TP4 TP5,5015,
TVS_SOD323F,D1,SOD323F,
